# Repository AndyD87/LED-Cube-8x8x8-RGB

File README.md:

# LED-Cube-8x8x8-RGB
LED-Cube Mikrocontroller Project
[Video of build Cube](https://www.youtube.com/watch?v=Oi0ap_jhWTA)
Next commit will comming soon. I'm reworking the code and prepare a SMD based LED-Cube.

## Notes
- LED-Cube with 512 RGB-LEDs in 8x8x8
- Controlled by a Microchip Microcontroller PIC18F4420
- Data for LED lighting is read from SD-Card over SPI
- Cube can be accessed from external source over UART.

## Background
Project was created in year 2009. It was my first bigger project i made.
Now it is getting reactivated, so i decided to publish it on github for a better organisation.

Because it was my first project, i had not that much expirience in how to program.
The code works great but it's still less documentated and has a chaotical structure. 
This get changed now!

## Bugs
- FTDI Chip don't work at the moment ( Hardware ) 

## ToDo
- Optimze the coding-style
- Switch microcontroller from PIC18F4420 to PIC18F4520 because of bigger Flash 
- Documentation!
- Support more SD-Cards by adding SDHC-Protocoll
- make API more simple.
- Make Sources independent from Cube x-y-z size

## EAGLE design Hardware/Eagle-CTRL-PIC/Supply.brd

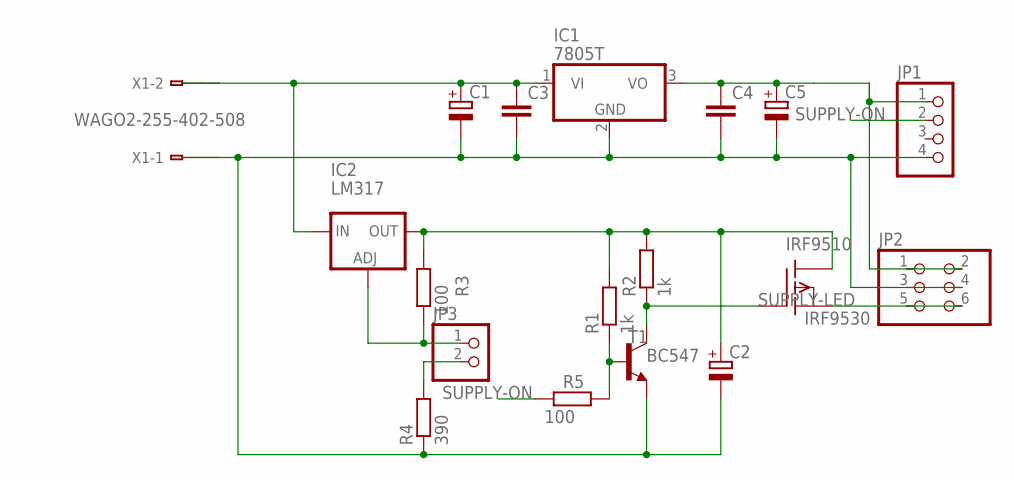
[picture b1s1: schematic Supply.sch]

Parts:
C1, C2: CPOL-EUE5-10.5; E5-10,5
C3, C4: C-EU050-024X044; C050-024X044
C5: CPOL-EUE2,5-6E; E2,5-6E
IC1: 7805T; TO220H
IC2: LM317; 317TL
IRF9510: IRF9530; TO220
JP1: PINHD-1X4; 1X04
JP2: PINHD-2X3; 2X03
JP3: PINHD-1X2; 1X02
R1, R2: 1k; 0207/7
R3, R5: 100; 0207/7
R4: 390; 0207/7
T1: BC547; TO92-CBE
X1: WAGO2-255-402-508; 255-402-508

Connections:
unnamed: C1.+, C3.1, IC1.1 (VI), IC2.3 (IN), X1.B2 (B1)
unnamed: IC2.1 (ADJ), JP3.1, R3.1
unnamed: C4.1, C5.+, IC1.3 (VO), JP1.1, JP2.1, JP2.2
unnamed: R1.1, R5.2, T1.B
unnamed: C1.-, C2.-, C3.2, C4.2, C5.-, IC1.2 (GND), JP1.4, JP2.3, JP2.4, R4.1, T1.E, X1.B1
unnamed: IRF9510.1 (G), R2.1, T1.C
unnamed: C2.+, IC2.2 (OUT), IRF9510.2 (D), R1.2, R2.2, R3.2
unnamed: JP3.2, R4.2
SUPPLY-LED: IRF9510.3 (S), JP2.5, JP2.6
SUPPLY-ON: JP1.2, R5.1

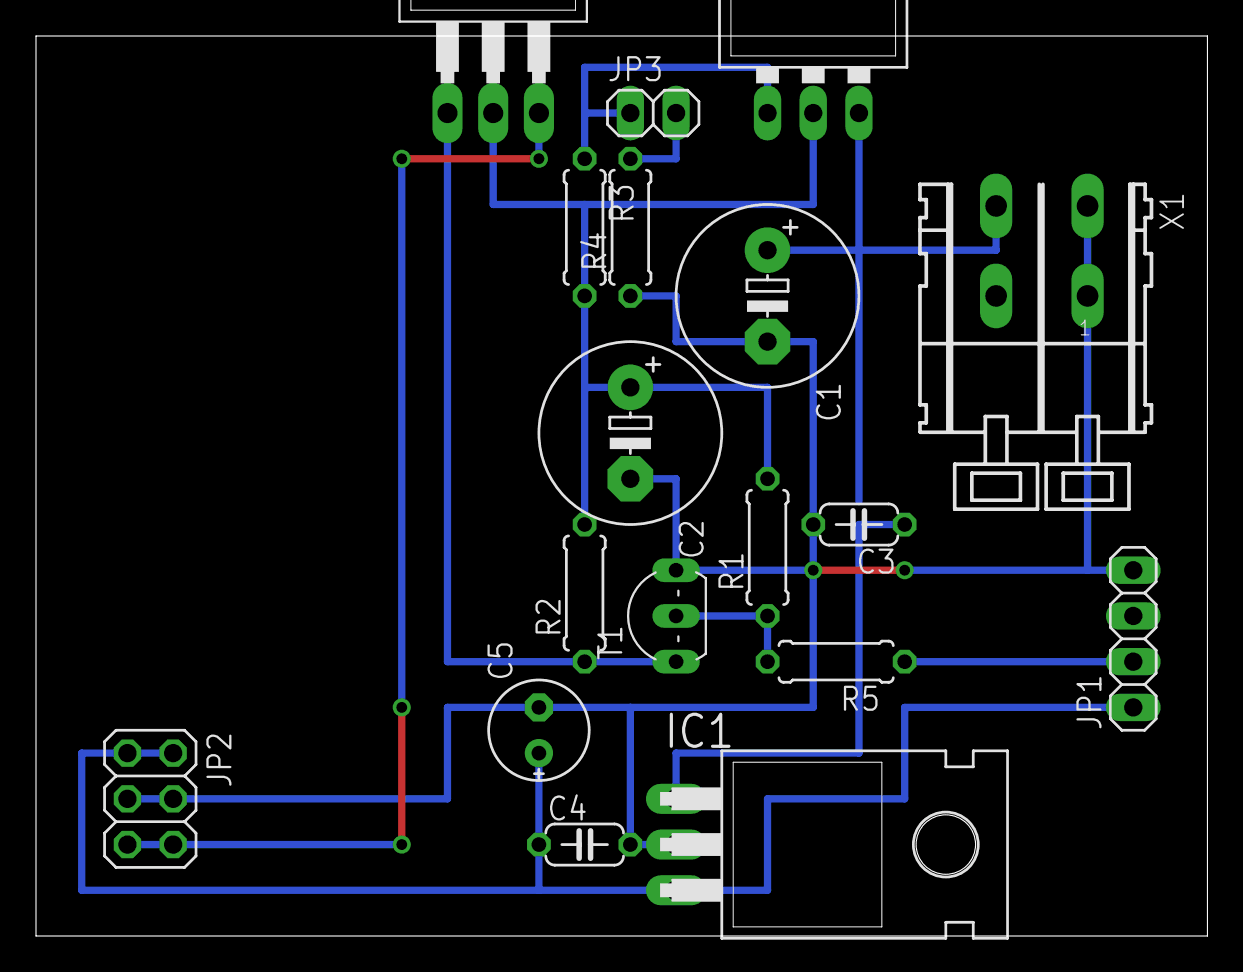
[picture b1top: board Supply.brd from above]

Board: 2 copper layers, 65.1 x 50.0 mm, 18 parts (0 on the bottom side), 10 nets.

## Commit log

2015-07-25 Files added.
    Start the project.
2015-07-26 Documentation and Name changes
    A lof of Comments, not yet enough.
    For better reading the files, changes are made on function names.
2015-07-26 Direcory structure changed
2015-07-26 Documentation
2015-07-26 Video added
2015-07-26 Rename Functions
2015-08-18 Files Removed and Ignored
2015-08-18 Files removed
